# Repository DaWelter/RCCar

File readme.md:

# RC Car Code and Schematics

This repository contains code and materials for my RC model car project. See [project page](https://hackaday.io/haxx).

## Structure of this repo
* app: The software for the command station and the vehicle, with the exception of ...
* bldcdriver: Firmware for my motor driver
* kicad: KiCad project files with the circuit schematics.
* packages: Common code in form of some python packages

## Dependencies

* _pygame_ - For joystick support
* _wifibroadcast_ - To send packets analog transmission style
* _pyqtgraph_ - Graphing
* _vext.pyqt4_ - Use system QT in a virtual env
* _posix_ipc_ - Communication with wifibroadcast
* [_cobs-python_](https://github.com/cmcqueen/cobs-python) - Message framing
* [_crc8_](https://github.com/niccokunzmann/crc8) or crc8cy - Error checking
* _protobuf_ - Message serialization
* _cython_ (0.28 from Feb. 2018 or later) - For crc8cy
* _boost-python_ - For h264decoder
* _libav_ - Video decoding
* [_minimu9-ahrs_](https://github.com/DavidEGrayson/minimu9-ahrs) - IMU readings for Raspberry Pi
* _pyquaternion_ - Coordinate transformation for IMU readings
* _socat_ - Communication via sockets

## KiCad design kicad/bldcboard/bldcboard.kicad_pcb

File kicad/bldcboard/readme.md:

BLDC driver project files
-------------------------

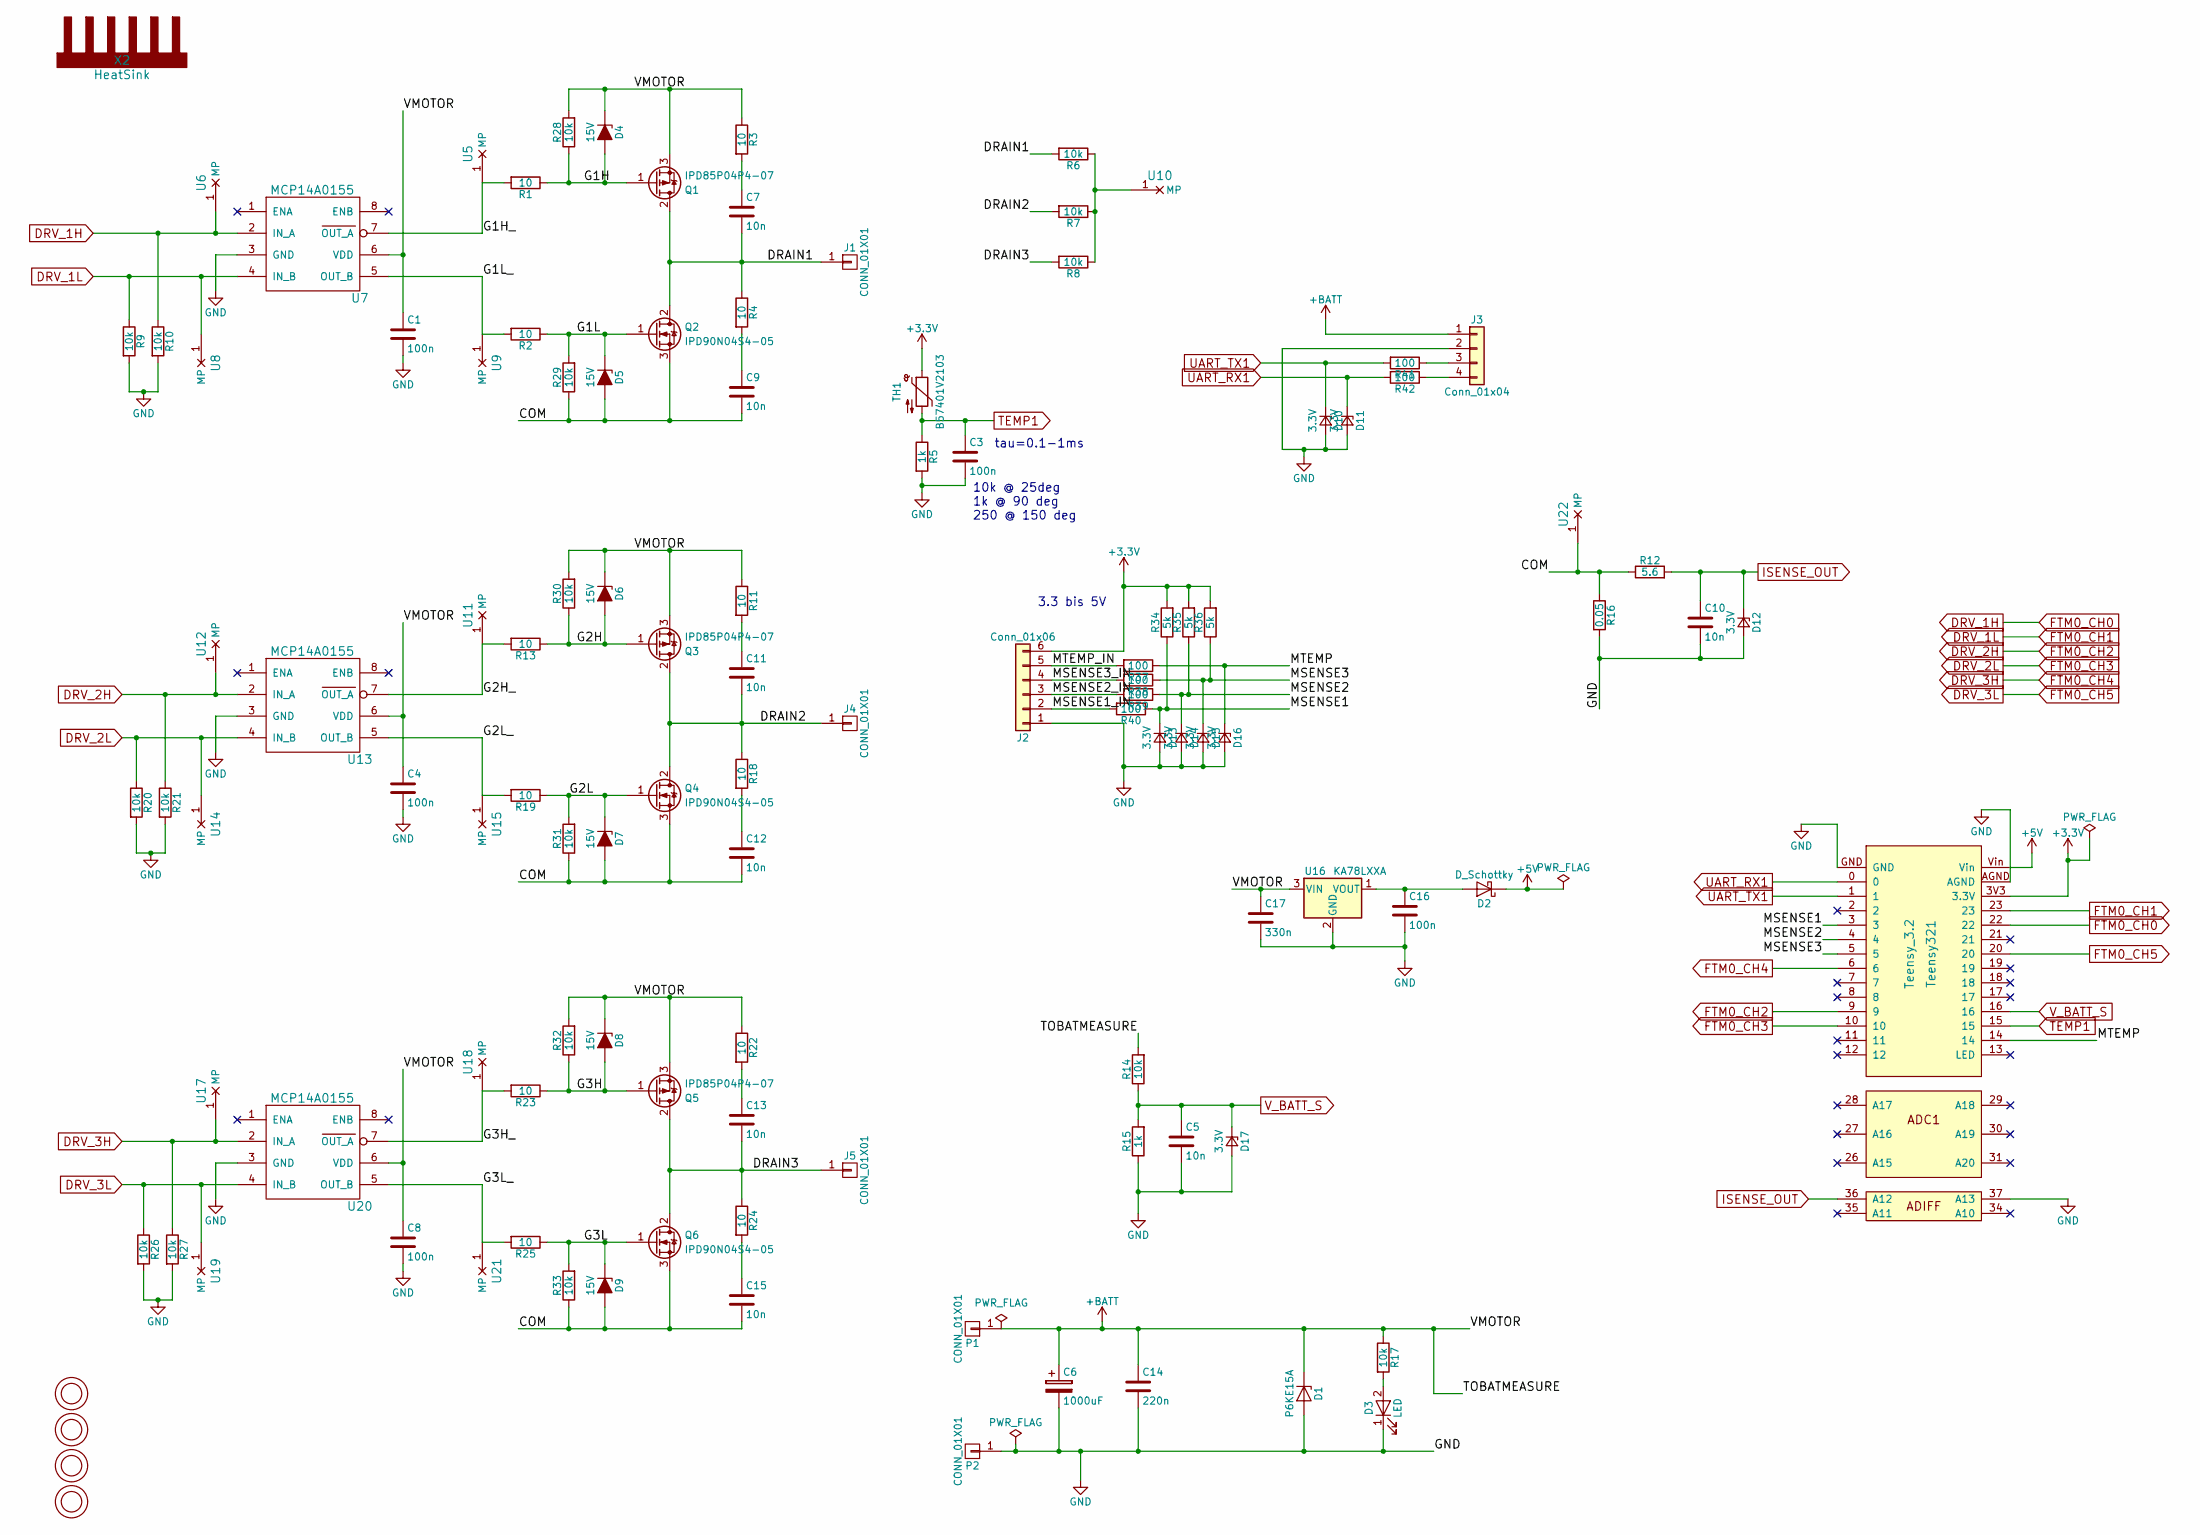
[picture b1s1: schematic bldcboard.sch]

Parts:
C1, C3, C4, C8, C16: 100n; C_0805_HandSoldering
C5, C7, C9, C10, C11, C12, C13, C15: 10n; C_0805_HandSoldering
C6: 1000uF; CP_Radial_D12.5mm_P5.00mm
C14: 220n; C_0805_HandSoldering
C17: 330n; C_0805_HandSoldering
D1: P6KE15A; D_DO-15_P5.08mm_Vertical_AnodeUp
D2: D_Schottky; D_DO-41_SOD81_P2.54mm_Vertical_KathodeUp
D3: LED; LED_0805
D4, D5, D6, D7, D8, D9: 15V; D_SOD-123
D10, D11, D12, D13, D14, D15, D16, D17: 3.3V; D_DO-35_SOD27_P2.54mm_Vertical_AnodeUp
J1, J4, J5: CONN_01X01; SolderPadBack_single_SMD_5x10mm
J2: Conn_01x06; JST_ZR_06x1.5mm_Straight_SMD
J3: Conn_01x04; Pin_Header_Angled_1x04_Pitch2.54mm
P1, P2: CONN_01X01; SolderPadBack_single_SMD_5x10mm
Q1, Q3, Q5: IPD85P04P4-07; TO-252-2_Rectifier
Q2, Q4, Q6: IPD90N04S4-05; TO-252-2_Rectifier
R1, R2, R3, R4, R11, R13, R18, R19, R22, R23, R24, R25: 10; R_0805_HandSoldering
R5, R15: 1k; R_0805_HandSoldering
R6, R7, R8, R9, R10, R14, R17, R20, R21, R26, R27, R28, R29, R30, R31, R32, R33: 10k; R_0805_HandSoldering
R12: 5.6; R_0805_HandSoldering
R16: 0.05; R_2512_HandSoldering
R34, R35, R36: 5k; R_0805_HandSoldering
R37, R38, R39, R40, R41, R42: 100; R_0805_HandSoldering
TH1: B57401V2103; R_0805_HandSoldering
Teensy321: Teensy_3.2; Teensy32
U1, U2, U3, U4: MountingHole; MountingHole_3.2mm_M3
U5, U6, U8, U9, U10, U11, U12, U14, U15, U17, U18, U19, U21, U22: MeasurePoint; Measurement_Point
U7, U13, U20: MCP14A0155; SOIC-8_3.9x4.9mm_Pitch1.27mm
U16: KA78LXXA; SOT-89-3_Handsoldering
X2: HeatSink; AK-VCX-01-Heatsink

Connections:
+3V3: J2.6, R34.2, R35.2, R36.2, TH1.1, Teensy321.3V3 (3.3V)
+5V: D2.1 (K), Teensy321.Vin
+BATT: C1.1, C4.1, C6.1, C8.1, C14.1, C17.1, D1.1 (K), D4.1 (K), D6.1 (K), D8.1 (K), J3.1, P1.1, Q1.3 (S), Q3.3 (S), Q5.3 (S), R3.1, R11.1, R14.2, R17.1, R22.1, R28.2, R30.2, R32.2, U7.6 (VDD), U13.6 (VDD), U16.3 (VIN), U20.6 (VDD)
/COM: C9.2, C12.2, C15.2, D5.2 (A), D7.2 (A), D9.2 (A), Q2.3 (S), Q4.3 (S), Q6.3 (S), R12.1, R16.1, R29.1, R31.1, R33.1, U22.1
/DRAIN1: C7.2, J1.1, Q1.2 (D), Q2.2 (D), R4.1, R6.2
/DRAIN2: C11.2, J4.1, Q3.2 (D), Q4.2 (D), R7.2, R18.1
/DRAIN3: C13.2, J5.1, Q5.2 (D), Q6.2 (D), R8.2, R24.1
/G1H: D4.2 (A), Q1.1 (G), R1.1, R28.1
/G1H_: R1.2, U5.1, U7.7 (OUT_A)
/G1L: D5.1 (K), Q2.1 (G), R2.1, R29.2
/G1L_: R2.2, U7.5 (OUT_B), U9.1
/G2H: D6.2 (A), Q3.1 (G), R13.1, R30.1
/G2H_: R13.2, U11.1, U13.7 (OUT_A)
/G2L: D7.1 (K), Q4.1 (G), R19.1, R31.2
/G2L_: R19.2, U13.5 (OUT_B), U15.1
/G3H: D8.2 (A), Q5.1 (G), R23.1, R32.1
/G3H_: R23.2, U18.1, U20.7 (OUT_A)
/G3L: D9.1 (K), Q6.1 (G), R25.1, R33.2
/G3L_: R25.2, U20.5 (OUT_B), U21.1
/MSENSE1: D13.1 (K), R34.1, R40.1, Teensy321.3
/MSENSE1_IN: J2.2, R40.2
/MSENSE2: D14.1 (K), R35.1, R39.1, Teensy321.4
/MSENSE2_IN: J2.3, R39.2
/MSENSE3: D15.1 (K), R36.1, R38.1, Teensy321.5
/MSENSE3_IN: J2.4, R38.2
/MTEMP: D16.1 (K), R37.1, Teensy321.14
/MTEMP_IN: J2.5, R37.2
DRV_1H: R10.1, Teensy321.22, U6.1, U7.2 (IN_A)
DRV_1L: R9.1, Teensy321.23, U7.4 (IN_B), U8.1
DRV_2H: R21.1, Teensy321.9, U12.1, U13.2 (IN_A)
DRV_2L: R20.1, Teensy321.10, U13.4 (IN_B), U14.1
DRV_3H: R27.1, Teensy321.6, U17.1, U20.2 (IN_A)
DRV_3L: R26.1, Teensy321.20, U19.1, U20.4 (IN_B)
GND: C1.2, C3.2, C4.2, C5.2, C6.2, C8.2, C10.2, C14.2, C16.2, C17.2, D1.2 (A), D3.1 (K), D10.2 (A), D11.2 (A), D12.2 (A), D13.2 (A), D14.2 (A), D15.2 (A), D16.2 (A), D17.2 (A), J2.1, J3.2, P2.1, R5.2, R9.2, R10.2, R15.1, R16.2, R20.2, R21.2, R26.2, R27.2, Teensy321.37 (A13), Teensy321.AGND, Teensy321.GND, U7.3 (GND), U13.3 (GND), U16.2 (GND), U20.3 (GND)
ISENSE_OUT: C10.1, D12.1 (K), R12.2, Teensy321.36 (A12)
unnamed: C7.1, R3.2
unnamed: C9.1, R4.2
unnamed: C11.1, R11.2
unnamed: C12.1, R18.2
unnamed: C13.1, R22.2
unnamed: C15.1, R24.2
unnamed: C16.1, D2.2 (A), U16.1 (VOUT)
unnamed: D3.2 (A), R17.2
unnamed: J3.3, R41.1
unnamed: J3.4, R42.1
unnamed: R6.1, R7.1, R8.1, U10.1
TEMP1: C3.1, R5.1, TH1.2, Teensy321.15
UART_RX1: D11.1 (K), R42.2, Teensy321.0
UART_TX1: D10.1 (K), R41.2, Teensy321.1
V_BATT_S: C5.1, D17.1 (K), R14.1, R15.2, Teensy321.16

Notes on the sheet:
3.3 bis 5V
tau=0.1-1ms
10k @ 25deg 1k @ 90 deg 250 @ 150 deg

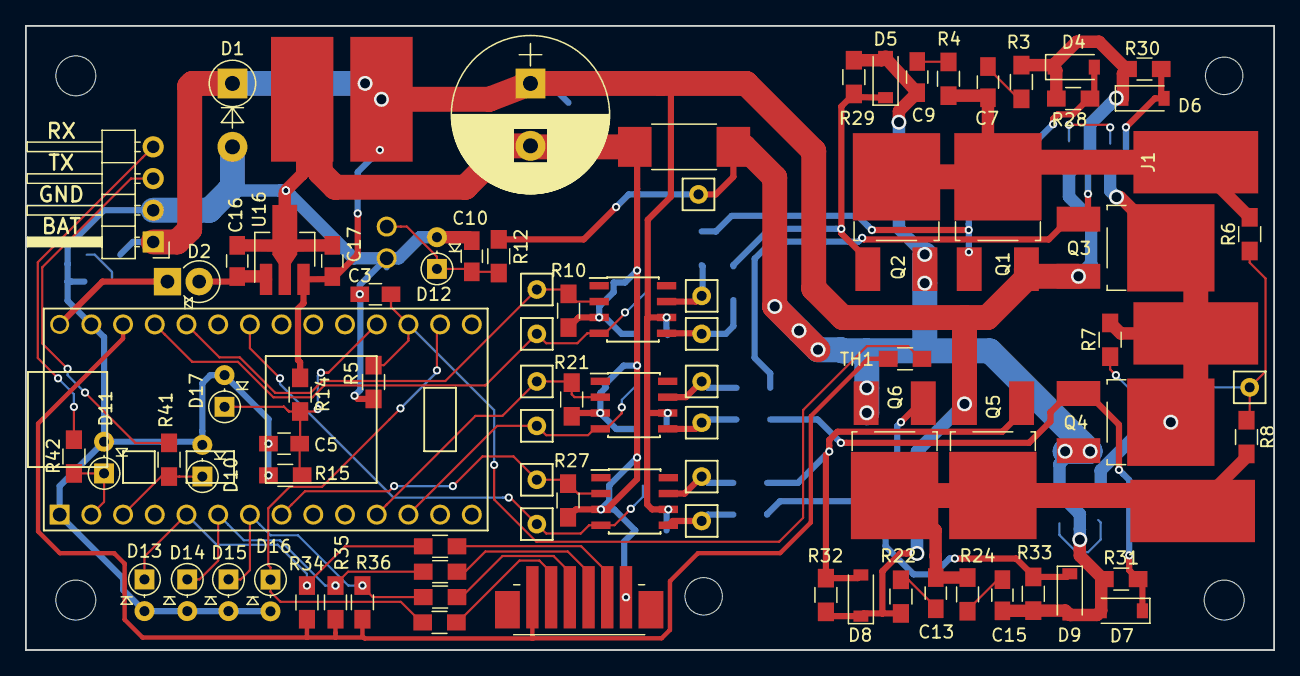
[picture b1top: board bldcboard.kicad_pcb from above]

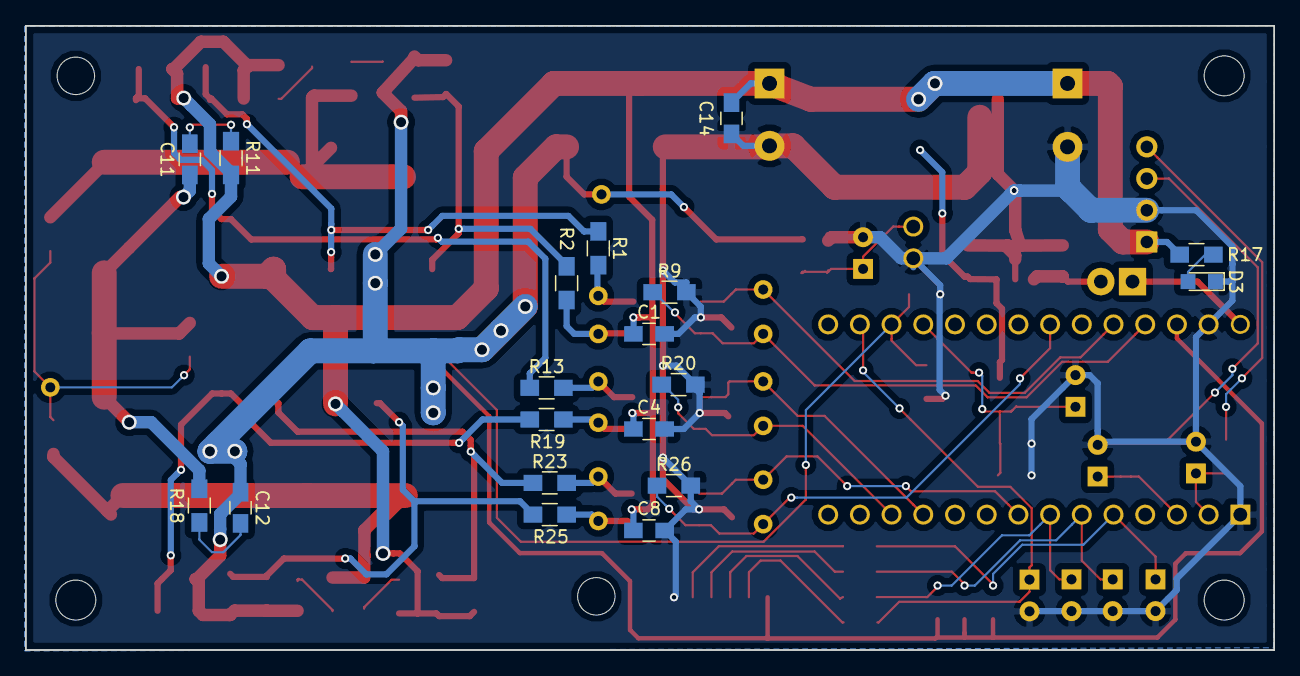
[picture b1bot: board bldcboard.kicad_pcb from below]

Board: 2 copper layers, 100.0 x 50.0 mm, 112 parts (19 on the bottom side), 50 nets.

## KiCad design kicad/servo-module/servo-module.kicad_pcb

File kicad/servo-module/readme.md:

Raspberry Pi shield project files
---------------------------------

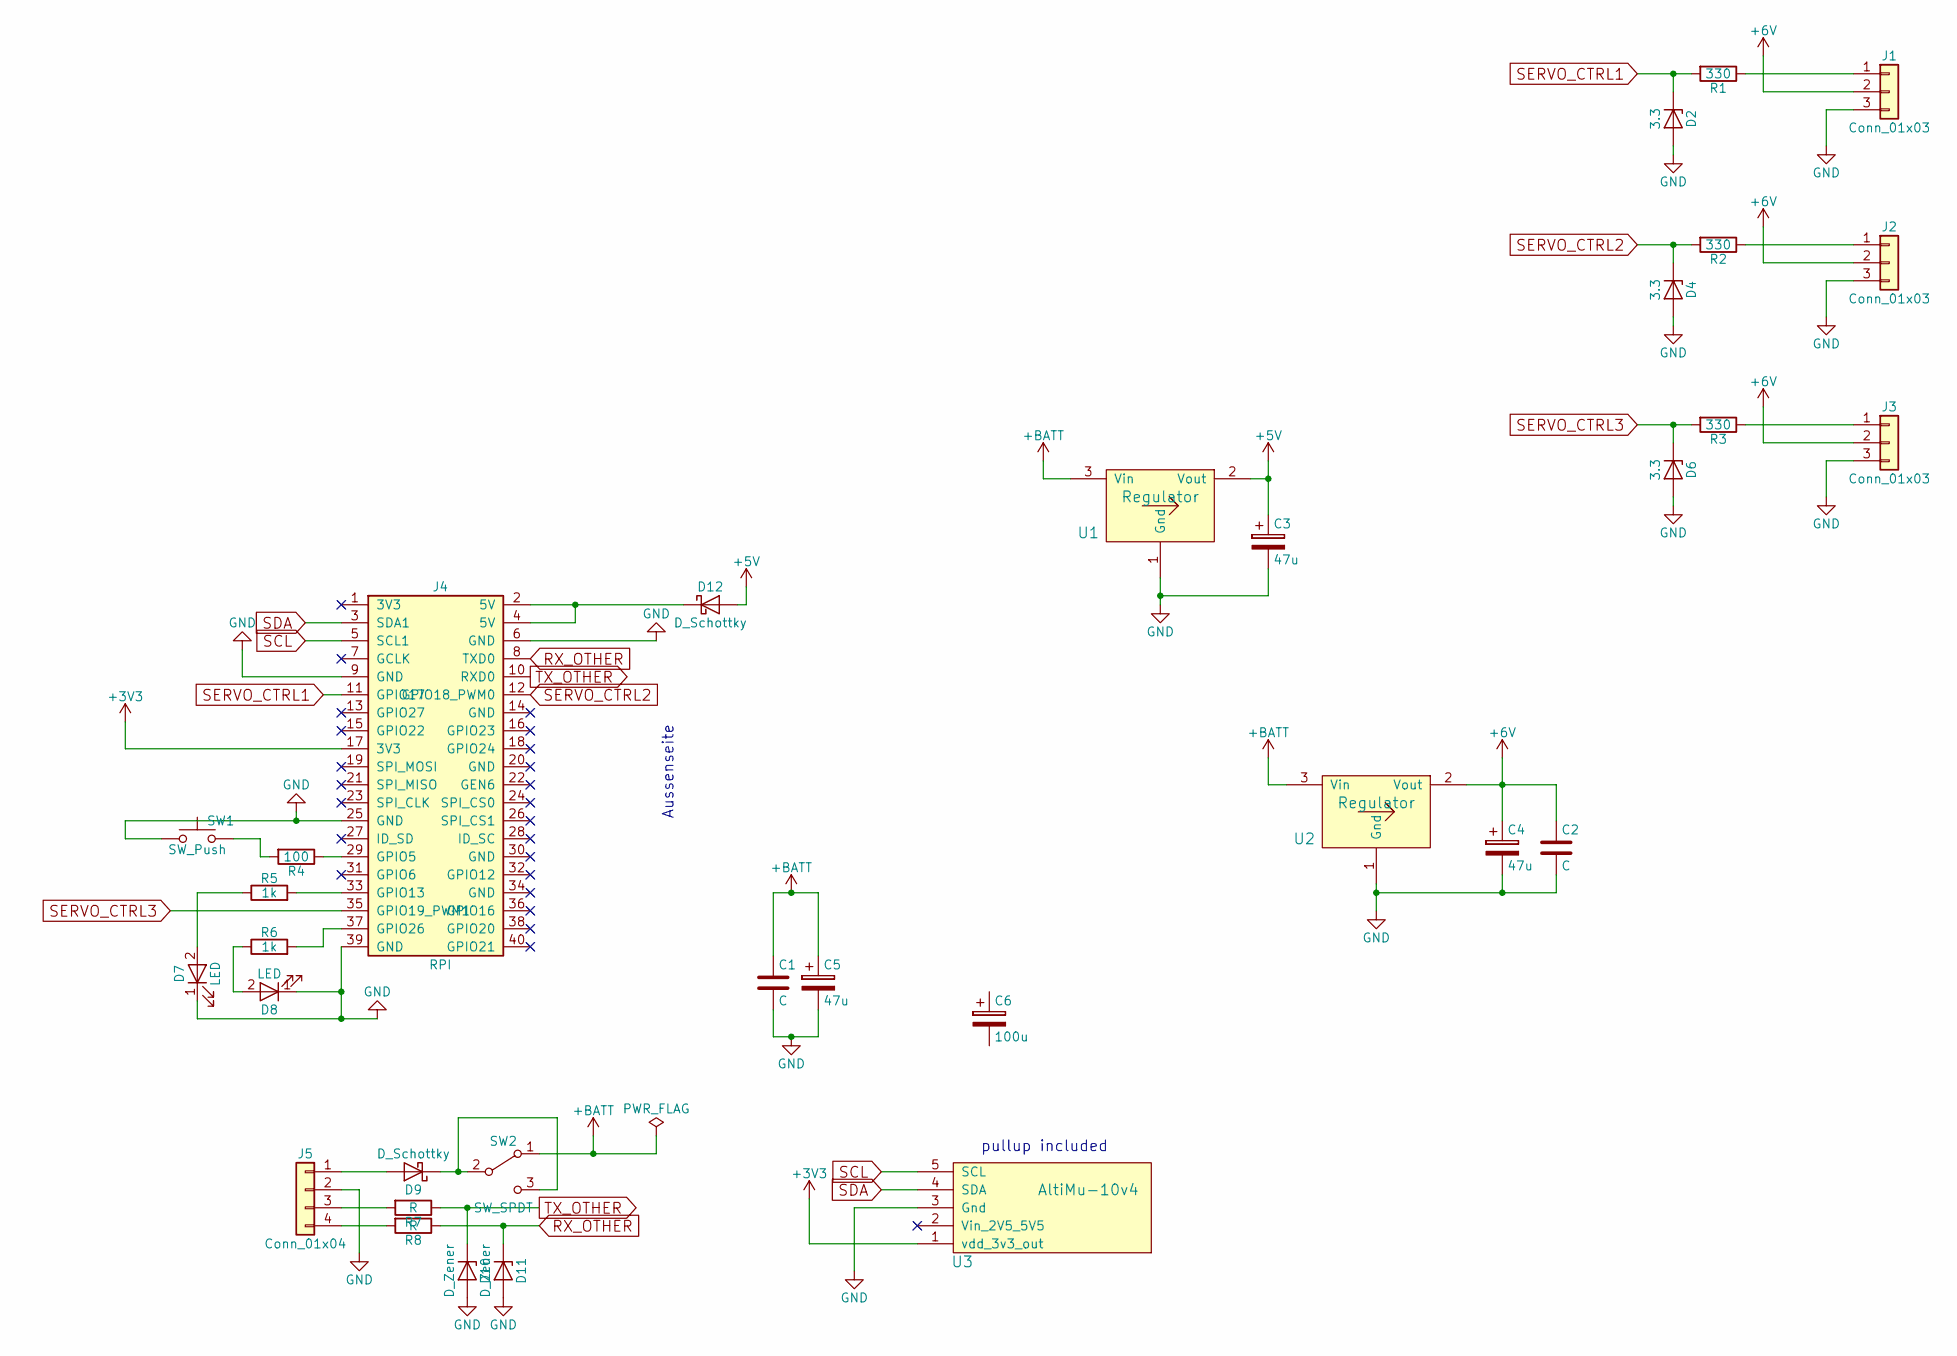
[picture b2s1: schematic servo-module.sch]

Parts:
C1, C2: C; C_Disc_D9.0mm_W2.5mm_P5.00mm
C3, C4, C5: 47u; CP_Radial_D5.0mm_P2.50mm
C6: 100u; CP_Radial_D8.0mm_P3.80mm
D2, D4, D6: 3.3; D_DO-35_SOD27_P2.54mm_Vertical_KathodeUp
D7, D8: LED; LED_D3.0mm
D9, D12: D_Schottky; D_DO-35_SOD27_P7.62mm_Horizontal
D10, D11: D_Zener; D_DO-35_SOD27_P2.54mm_Vertical_KathodeUp
J1, J2, J3: Conn_01x03; Pin_Header_Straight_1x03_Pitch2.54mm
J4: RPI; RPI3_Header
J5: Conn_01x04; Pin_Header_Straight_1x04_Pitch2.54mm
R1, R2, R3: 330; R_Axial_DIN0207_L6.3mm_D2.5mm_P7.62mm_Horizontal
R4: 100; R_Axial_DIN0207_L6.3mm_D2.5mm_P7.62mm_Horizontal
R5, R6: 1k; R_Axial_DIN0207_L6.3mm_D2.5mm_P7.62mm_Horizontal
R7, R8: R; R_Axial_DIN0207_L6.3mm_D2.5mm_P7.62mm_Horizontal
SW1: SW_Push; SW_PUSH_6mm
SW2: SW_SPDT; Switch
U1, U2: Regulator; ChinaReglerV2
U3: AltiMu-10v4; Pololu-AltiMu-10-v4

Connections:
+3V3: J4.17 (3V3), U3.1 (vdd_3v3_out)
+5V: C3.1, D12.2 (A), U1.2 (Vout)
+6V: C2.1, C4.1, J1.2, J2.2, J3.2, U2.2 (Vout)
+BATT: C1.1, C5.1, SW2.1 (A), U1.3 (Vin), U2.3 (Vin)
GND: C1.2, C2.2, C3.2, C4.2, C5.2, D2.2 (A), D4.2 (A), D6.2 (A), D7.1 (K), D8.1 (K), D10.2 (A), D11.2 (A), J1.3, J2.3, J3.3, J4.6 (GND), J4.9 (GND), J4.25 (GND), J4.39 (GND), J5.2, SW1.1, U1.1 (Gnd), U2.1 (Gnd), U3.3 (Gnd)
unnamed: D7.2 (A), R5.1
unnamed: D8.2 (A), R6.1
unnamed: D9.1 (K), SW2.2 (B), SW2.3 (C)
unnamed: D9.2 (A), J5.1
unnamed: D12.1 (K), J4.2 (5V), J4.4 (5V)
unnamed: J1.1, R1.1
unnamed: J2.1, R2.1
unnamed: J3.1, R3.1
unnamed: J4.29 (GPIO5), R4.1
unnamed: J4.33 (GPIO13), R5.2
unnamed: J4.37 (GPIO26), R6.2
unnamed: J5.3, R7.2
unnamed: J5.4, R8.2
unnamed: R4.2, SW1.2
RX_OTHER: D11.1 (K), J4.8 (TXD0), R8.1
SCL: J4.5 (SCL1), U3.5 (SCL)
SDA: J4.3 (SDA1), U3.4 (SDA)
SERVO_CTRL1: D2.1 (K), J4.11 (GPIO17), R1.2
SERVO_CTRL2: D4.1 (K), J4.12 (GPIO18_PWM0), R2.2
SERVO_CTRL3: D6.1 (K), J4.35 (GPIO19_PWM1), R3.2
TX_OTHER: D10.1 (K), J4.10 (RXD0), R7.1

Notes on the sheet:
pullup included
Aussenseite

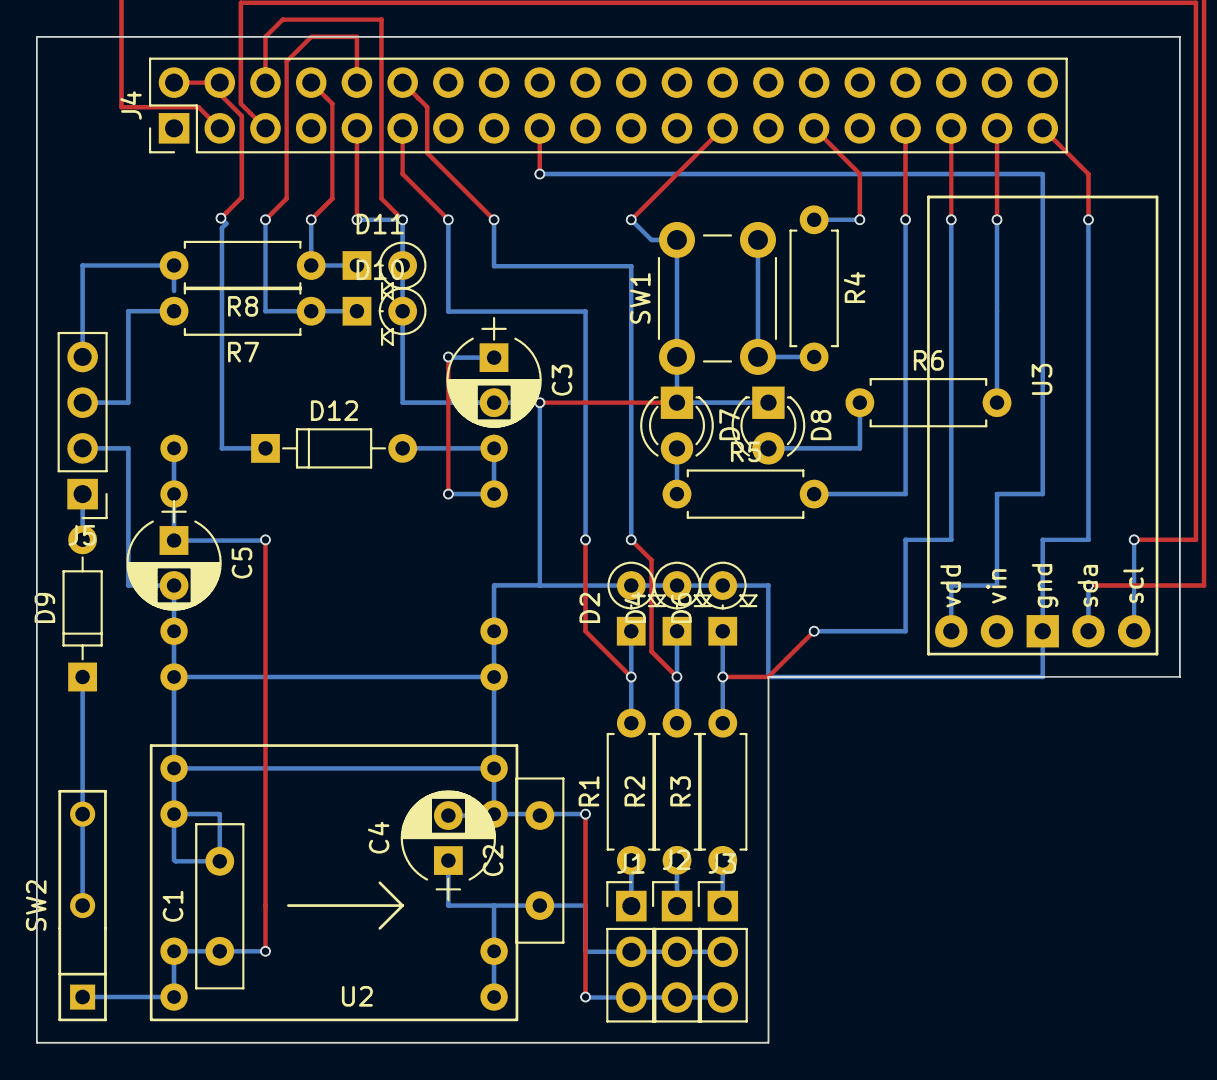
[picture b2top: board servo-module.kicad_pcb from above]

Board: 2 copper layers, 63.5 x 55.9 mm, 32 parts (1 on the bottom side), 26 nets.

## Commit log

2018-10-06 Initial import
2018-10-06 Add Kicad schematics
2018-10-06 Doh ... .gitignore hid important things.
2018-10-06 Add missing example config
2018-10-06 Turn protocobs into a module - it shall not be a package - because only it's only one file.
2018-10-07 Removed record function. It should probably record on the vehicle instead of on the receiver.
2018-10-07 Better status line with (wrong) euler angle reading and functional display of load and connection quality
2018-10-07 Add display for remaining stats and make plots a bit prettier.
2018-10-07 Attempt to print somewhat correct heading, pitch, roll angles. Unsure about the euler convention minimu9-ahrs uses. Does not appear to be aerospace convention. Pitch goes beyond -90 to 90. So a bette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
2018-10-09 Use wasd controls and enable camera yaw control with arrow keys
2018-10-13 Higher motor power and speed limit!
2018-10-13 Graphing speed setpoint together with actual speed.
2018-10-14 Tweaked servo range
2018-10-14 Attempt to make the wifi boot into monitor mode
2018-10-18 A different joystick control scheme
2018-10-20 Better camera movement by low pass filtering
2018-10-20 Add display of receive data rate. Use both telemetry and video ports for that.
2018-10-20 Add option for retransmission
2018-10-25 Documents updated
2018-10-25 Shutdown button for keyboard control. Nicer integrator implementation (special feature to restrict output to either positive or negative values, switch between side only possible when output reaches 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
2018-10-25 Slightly saner code for arithmetic graph
2018-10-25 A button to turn transmission off, effectively shutting off the motor controller when it does not receive commands any more
